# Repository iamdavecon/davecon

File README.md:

# /home

- [main site](https://iamdavecon.github.io/)
- [discord aka Davecord](https://discord.gg/BdCQY2533X)

## Code of conduct

**Don't be an asshole**

## Release Notes

- [V](https://docs.google.com/document/d/1AGmxOIIG9FJRUuFvxuajCBeXXvTiyNuTyO-RnFlCKv4)
- [4.2](https://docs.google.com/document/d/1AzK0nzqCdaiZECCq4kKoY3V3NjuLak1vkBxOy_BbJ88)
- [3.14](https://docs.google.com/document/d/1oaGeMpaKX69vDvRT8u-n9noyw66Tj9VWQcM_10Sb85A)
- [2.1](https://docs.google.com/document/d/19L7Xp_Kvz2vSCQtCk9RlQ3hHlzpowm8FXnbNuoqx-NI)
- [1.0](https://docs.google.com/document/d/10pknMyp7eMQa5K1S5WkilPujUupOhHGwtNkq9URTMqg)
- [0.0 (beta)](https://docs.google.com/document/d/1GsItmplrJTlb02CClvNM4Jv8sW6bOXMFimozth7cOLA/edit#bookmark=id.o19r0bhabfy6)

## Badge Art

### DC30 (1.0)

| Front | Back |
| --- | --- |
|  |  |

### DC31 (2.1)

| Front | Back |
| --- | --- |
|  |  |

### DC32 (3.14)

| Front | Back |
| --- | --- |
|  |  |

### DC33 (4.2)

| Front | Back |
| --- | --- |
|  |  |

### DC34 (V)

| Front | Back |
| --- | --- |
|  |  |

### DC35 (6.6.6)

| Front | Back |
| --- | --- |
|  |  |

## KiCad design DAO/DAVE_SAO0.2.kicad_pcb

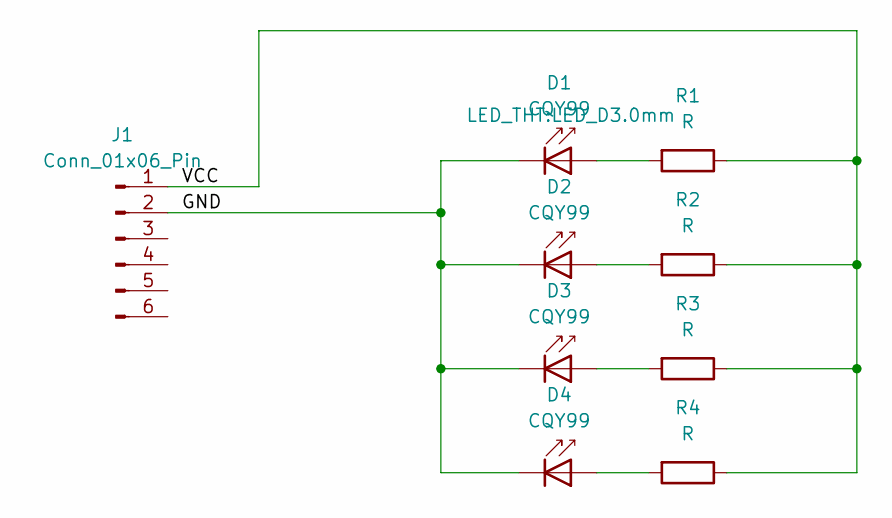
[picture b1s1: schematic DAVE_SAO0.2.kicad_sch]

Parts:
D1, D2, D3, D4: CQY99; LED_D3.0mm
J1: Conn_01x06_Pin; PinHeader_2x03_P2.54mm_Vertical_SMD
R1, R2, R3, R4: R; R_2512_6332Metric_Pad1.40x3.35mm_HandSolder

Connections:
/GND: D1.1 (K), D2.1 (K), D3.1 (K), D4.1 (K), J1.2
/VCC: J1.1, R1.1, R2.1, R3.1, R4.1
unnamed: D1.2 (A), R1.2
unnamed: D2.2 (A), R2.2
unnamed: D3.2 (A), R3.2
unnamed: D4.2 (A), R4.2

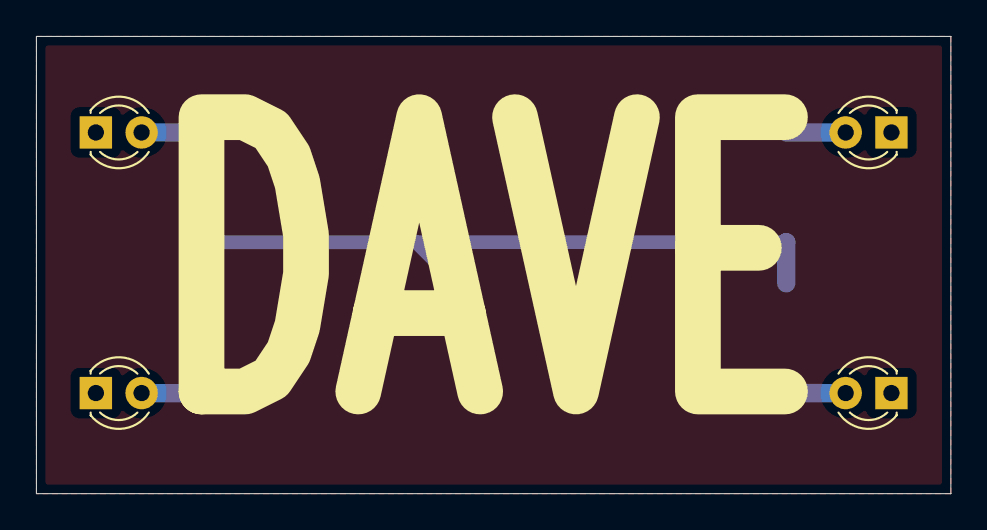
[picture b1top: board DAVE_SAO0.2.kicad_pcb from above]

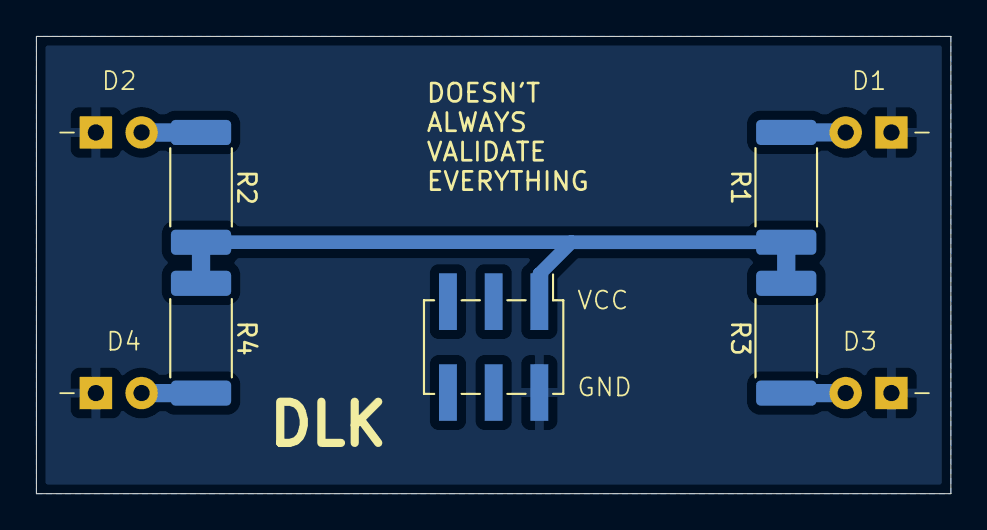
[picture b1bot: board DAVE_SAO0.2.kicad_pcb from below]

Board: 2 copper layers, 50.8 x 25.4 mm, 9 parts (5 on the bottom side), 6 nets.

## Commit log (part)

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2024-07-18 Updates for 2.1
2024-07-30 Add 3.14 planning
2024-08-09 Add DC32 content
2024-08-11 added davecon rom
2024-08-11 davecon flipped roms
2024-08-15 Add DC32 writeup
2024-08-16 Add DaveCon4 badge draft
2024-08-18 update FAQ
2024-11-28 update mastodon
2024-12-26 Add cyod link
2025-08-01 Add t-shirt link
2025-08-08 Add link to PepperCon discord
2025-08-14 Add DC33 badge designs
2025-08-15 Add 4.2
2025-08-16 Add DaveTracker
2025-09-04 add badge template (gimp)
2026-04-16 add playlist
2026-06-15 add link to main site
